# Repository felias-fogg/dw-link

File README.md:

# dw-link 

This Arduino sketch turns your Arduino UNO into a hardware debugger for the classic ATtinys and the ATmegaX8s, such as the ATmega328. It gives you a chance to find out how it feels to use a source-level debugger on an Arduino Uno or an ATtiny board. Do you want to give it a try? Use the *quick-start guide* in the [dw-link manual](https://felias-fogg.github.io/dw-link/) to see if it works for you. 

From version 7 on, the protocol has been changed from [GDB RSP](https://sourceware.org/gdb/current/onlinedocs/gdb.html/Remote-Protocol.html) to a variant of the JTAGICE mkII protocol ([AVR067](https://www.microchip.com/en-us/application-notes/an2587-1)), which implies that you necessarily have to use [PyAvrOCD](https://pyavrocd.io) (version >= 2.0.0) as a GDB server. If you want to connect GDB to dw-link using only the serial line, you need to fall back to version 6.

This repository, which is organized as an Arduino library, contains the following directories:

* [**src**](src/) contains an empty header file so that it fits the format of a library,
* [**examples**](examples/) contains 
  * the [dw-link](examples/dw-link/) sketch, the debugger firmware, and 
  * the [testprobe](examples/testprobe/) sketch, which can be used to run tests on a freshly assembled dw-link probe shield,
* [**docs**](docs/) contains the documentation files for the [manual](https://felias-fogg.github.io/dw-link/),
* [**extras**](extras/) contains the folder [pcb](extras/pcb/) with design data (KiCad) for the optional dw-link probe.

<sup><sub>The cover picture was designed based on vector graphics by [captainvector at 123RF](https://de.123rf.com/profile_captainvector).</sub></sup>

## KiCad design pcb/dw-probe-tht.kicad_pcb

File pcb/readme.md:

# The *dw-link probe*: Hardware for dw-link

<br />This work is licensed under a <a rel="license" href="http://creativecommons.org/licenses/by/4.0/">Creative Commons Attribution 4.0 International License</a>.

When you want to debug your projects using dw-link more than once, it is a good idea to have a hardware solution. For instance, an Arduino shield. As described in the manual, you can just assemble a solution on a prototype board, which works for 5 V projects with less than 20 mA of supply current. 

The current design of the *dw-link probe* is more ambitious, but far from an industrial-strength hardware debugging tool as, e.g., Atmel ICE. The limitations for the target boards are:

* 3.3 to 5 V supply voltage (but not lower),
* reasonable loads on the SPI lines, e.g., an LED and a 1 kΩ series resistor (but no stronger resistor),
* no capacitive load on the RESET line of the target,
* no loads higher than a 10 kΩ resistance on the RESET line,
* minimum target MCU clock frequency of 4 kHz.

If these constraints are met, the dw-link probe should work.  Otherwise, one might encounter strange behavior and/or error messages. 

The current version (V3.1) of the dw-link probe (an Arduino UNO shield) uses mainly THT components, which should make it easy to assemble it using [these instructions](assembly.md). The three SMD components can also be hand-soldered to the PCB since the solder pads are extra large. 

**Note:** It is advisable to solder an additional 100 µF or more capacitor between 5V and GND. Otherwise, the hardware debugger might brown out when power-cycling the target, and you will need to disconnect and reconnect.

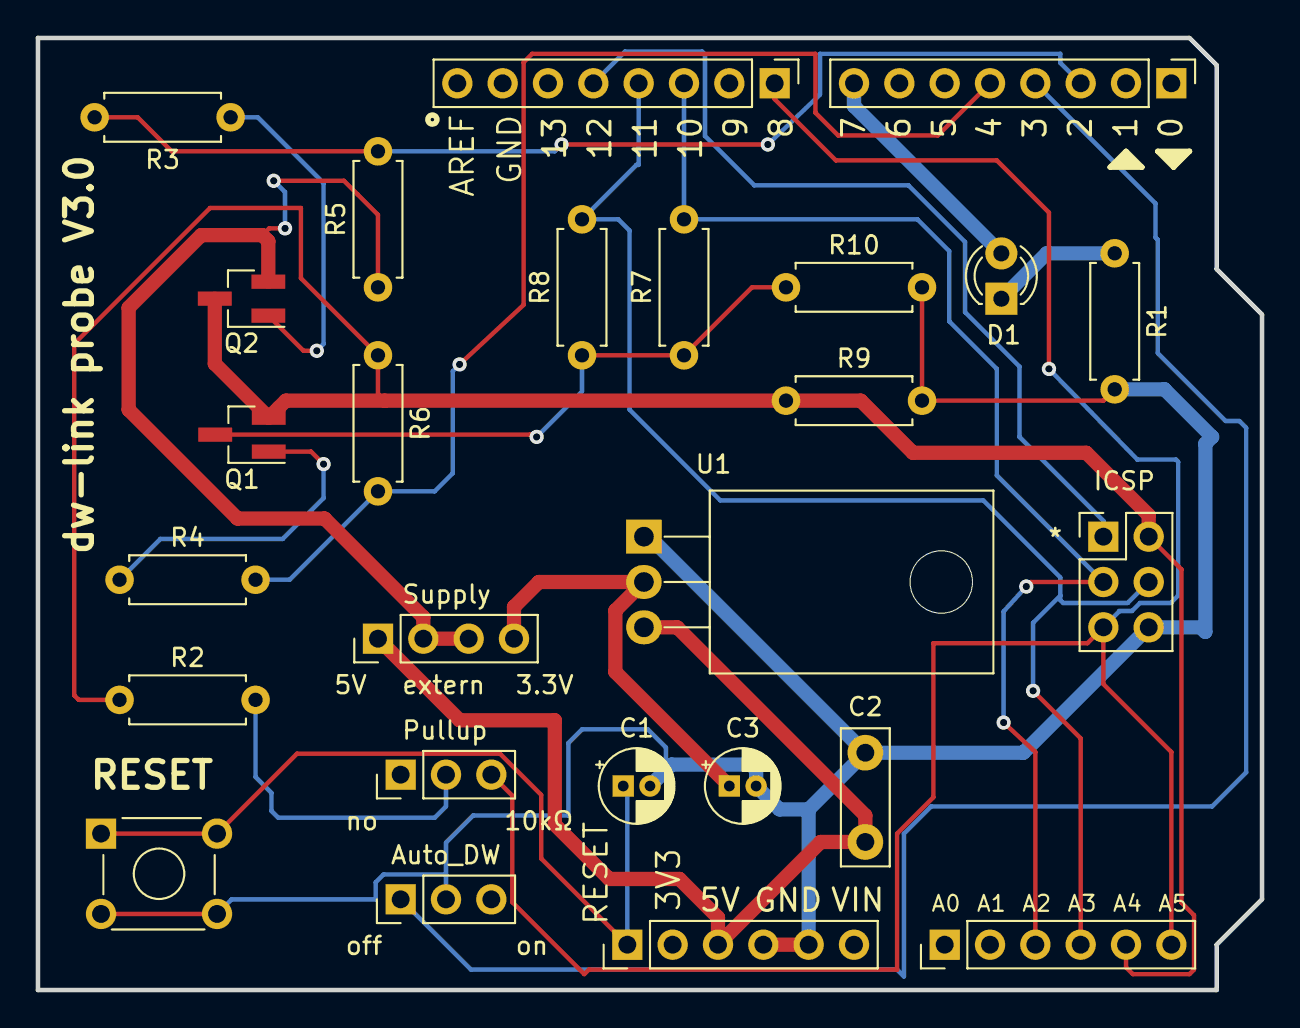
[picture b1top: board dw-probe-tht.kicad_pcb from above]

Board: 2 copper layers, 68.6 x 53.3 mm, 26 parts (0 on the bottom side), 19 nets.

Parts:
AD1: PINHD-1X6; PinHeader_1x06_P2.54mm_Vertical
Auto_DW1: Conn_01x03; PinHeader_1x03_P2.54mm_Vertical
C1, C3: 10µF; CP_Radial_D4.0mm_P1.50mm
C2: 100nF; C_Disc_D7.5mm_W2.5mm_P5.00mm
D1: LED; LED_D3.0mm
IOH1: PINHD-1X8; PinHeader_1x08_P2.54mm_Vertical
IOL1: PINHD-1X8; PinHeader_1x08_P2.54mm_Vertical
JP1: ARDUINO_CONN-ICSP; PinHeader_2x03_P2.54mm_Vertical
POWER1: PINHD-1X6; PinHeader_1x06_P2.54mm_Vertical
Pullup1: Conn_01x03; PinHeader_1x03_P2.54mm_Vertical
Q1, Q2: IRLML6402; SOT-23_Handsoldering
R1: 1kΩ; R_Axial_DIN0207_L6.3mm_D2.5mm_P7.62mm_Horizontal
R2, R5, R6: 10kΩ; R_Axial_DIN0207_L6.3mm_D2.5mm_P7.62mm_Horizontal
R3, R4: 220Ω; R_Axial_DIN0207_L6.3mm_D2.5mm_P7.62mm_Horizontal
R7, R8: 680Ω; R_Axial_DIN0207_L6.3mm_D2.5mm_P7.62mm_Horizontal
R9, R10: 10MΩ; R_Axial_DIN0207_L6.3mm_D2.5mm_P7.62mm_Horizontal
SW1: SW_Push; SW_TH_Tactile_Omron_B3F-10xx
Supply1: Conn_01x04; PinHeader_1x04_P2.54mm_Vertical
U1: LM1117T-3.3; TO-220-3_Horizontal_TabDown

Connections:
GND: Auto_DW1.2, C1.2, C2.2, C3.2, IOH1.7, JP1.6, POWER1.4, POWER1.5, R1.2, R9.2, R10.2, SW1.2, U1.1 (GND)
unnamed: AD1.3, IOH1.3, JP1.3, R7.2
unnamed: AD1.4, IOH1.4, JP1.4, R8.2
unnamed: Auto_DW1.1, IOL1.4
unnamed: C1.1, POWER1.1, SW1.1
unnamed: D1.2 (A), IOL1.8
unnamed: D1.1 (K), R1.1
unnamed: IOH1.5, JP1.1
unnamed: IOL1.3, R3.2, R5.2
unnamed: IOL1.5, R4.2, R6.2
unnamed: Pullup1.2, R2.2
unnamed: AD1.6, IOH1.1, JP1.5, Pullup1.3
unnamed: Q1.3 (D), R7.1, R8.1, R10.1
unnamed: Q1.1 (G), R4.1
unnamed: Q2.1 (G), R3.1
unnamed: Q2.2 (S), R5.1, Supply1.2, Supply1.3
unnamed: C2.1, POWER1.3, Supply1.1, U1.3 (VI)
unnamed: C3.1, Supply1.4, U1.2 (VO)
VCC: AD1.5, JP1.2, Q1.2 (S), Q2.3 (D), R2.1, R6.1, R9.1

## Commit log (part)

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2021-11-24 V 1.0.2 - without build files
2021-11-30 V1.0.3
2021-12-02 V1.0.4
2021-12-04 V1.0.5
2021-12-07 V1.0.6
2021-12-10 V1.0.7
2021-12-11 V1.0.8
2021-12-20 V1.0.9
2021-12-27 V1.1.0
2021-12-29 V1.1.1
2021-12-30 V1.1.2
2021-12-30 V1.1.3
2021-12-31 V1.1.4 - public release
2021-12-31 changelog updated
2021-12-31 readme updated
2021-12-31 added workflow
2021-12-31 corrected workflow
2021-12-31 V1.1.5
2022-01-03 V1.1.6
2022-01-03 V1.1.6 - missing pic
2022-01-03 V1.1.6 - workflow change
2022-01-03 V1.1.6 - unit tests removed
2022-01-03 V1.1.6 - workflow changed
2022-01-04 V1.1.7
2022-01-04 V1.1.8
2022-01-05 V1.1.9
2022-01-05 V1.1.9 - updated docu
2022-01-05 V1.1.10
2022-01-06 manual update
2022-01-08 update pcb and doc
2022-01-08 blockusb branch
2022-01-09 V1.1.11
2022-01-09 pic update
2022-01-09 updated workflow
2022-01-11 V1.1.12
2022-01-11 V1.1.12 - dwlink nano fix
2022-01-15 V1.2.0
2022-01-15 V1.2.0.a
2022-01-15 V1.2.1
2022-01-15 V1.2.2
2022-01-17 V1.2.3
2022-01-17 V1.2.4
2022-01-17 manual - wiring fix
2022-01-19 V1.2.5
2022-01-19 V1.2.5 - workflow
2022-01-19 V1.3.0
2022-01-20 V1.3.1
2022-01-20 V1.3.2
2022-01-20 V1.3.3
2022-01-22 V1.3.4
2022-01-23 V1.3.5
2022-01-26 V1.3.6
2022-02-02 V1.3.7
2022-02-02 optimized PDF file
2022-02-02 V1.3.7 (updated)
2022-02-02 V1.3.7 (manual updated)
2022-02-04 V1.3.8
2022-02-17 V1.3.9
2022-03-12 platformio debugging calls 'mo dwconnect'
2022-03-12 V1.3.10
2022-03-13 Changed gitignore
2022-11-24 Disable pull up on TMOSI upon disableSpiPins()
2023-01-07 Added symbolic link from src to dw-link to make platformio build possible
2023-08-11 V2.0.0
2023-08-11 fixed some inconsistencies
2023-08-15 V2.1.0
2023-08-15 V2.1.2
2023-08-15 V2.1.2 (incl. documentation)
2023-08-16 V2.1.3
2023-08-16 V2.1.4
2023-08-17 V2.1.5
2023-08-18 V 2.1.6
2023-08-20 V2.1.7
2023-08-21 V2.1.8
2023-08-22 dw-server and documentation
2023-08-22 fixed typos in quickstart
2023-08-22 readme fixes
2023-08-22 quzickstart fixes
2023-08-23 added checks to quickstart
2023-08-23 V2.1.9
2023-08-23 readme fix
2023-08-24 docu update
2023-08-24 workflow update
2023-08-26 changelog ficed
2023-08-26 Revert "workflow update"
    This reverts commit 78d8907c8fad9df0ea710d77213ca2aa1fff75bf.
2023-08-26 re-apply workflow changes
2023-08-27 docu extended
2023-08-27 pcb fix
2023-08-27 .gitignore removed from repo
2023-08-27 V2.2.0
2023-08-27 V2.2.1
2023-08-28 V2.3.0
2023-08-28 V3.0.0
2023-08-28 changelog
2023-08-28 manual fix
2023-08-28 .gitignore
2023-08-29 V3.0.1
2023-08-29 quickstart pdf
2023-08-29 quickstart update
2023-08-29 Manual and Quickstart fixes
2023-08-29 Quickstart fixes
2023-08-29 quickstart
2023-09-05 V3.1.0
2023-09-06 V3.1.1
2023-09-06 readme
2023-09-06 docs
2023-09-09 PCB & docu
2023-09-10 documentation update
2023-09-11 assembly update
2023-09-11 V3.3.0
2023-09-11 changelog fix
2023-09-11 CS2 fix
2023-09-12 V3.4.0
2023-09-13 low frequency
2023-09-13 V3.5.0
2023-09-13 V3.5.1
2023-09-15 V3.5.2
2023-09-18 testprobe
2023-09-20 new dw-link probe V3.1
2023-09-20 new example, restored pics
2023-09-21 description of debugging UNO with serial connection
2023-09-21 adapted to new gede version
2023-09-22 manual toubleshooting: ISP programmer failure
2023-09-23 V3.5.3
2023-09-23 going back to my version of gede
2023-09-25 readme update
2023-10-05 manual
2023-12-18 documentation adapted, in particular new schemativ for probe
2024-02-25 V3.5.4
2024-12-16 V3.5.5
2024-12-16 quickstart.pdf update
2024-12-17 V3.5.6
2024-12-23 V4.0.0 - with Arduino IDE 2.0 support
2024-12-28 V4.0.0
2024-12-29 all tool files ready to roll
2024-12-29 tools files moved to felias-fogg.github.io
2024-12-30 added quickstart link
2024-12-30 edited quickstarts
2024-12-31 core mods adapted, MiniCore works
2024-12-31 readme updates + core-mods fixes
2025-01-01 V4.0.1
2025-01-02 V4.0.2
2025-01-02 update manual
2025-01-06 V4.0.3
2025-01-06 updated docs + dw-server for Linux
2025-01-07 assembly notes adapted and testprobe.ino extended
2025-01-07 quickstart hardlink
2025-01-07 update doc because of windows hickup
2025-01-08 doc update and Windows tool issue mitigation
2025-01-08 doc update
2025-01-16 V4.0.4
2025-01-18 V4.1.0
2025-01-19 V4.2.0
2025-01-19 update changelog
2025-02-01 V4.3.0
2025-02-01 V4.3.1
2025-02-10 V4.4.0
2025-02-14 manual V4.4.0
2025-02-26 V4.5.0
2025-03-27 V5.0.0-pre1
2025-03-28 v5.0.0-pre2
2025-04-16 v5.0.0
2025-04-17 v5.1.0
2025-07-22 v5.2.0
2025-07-29 ISPMON removed
2025-07-30 v5.2.1
2025-07-31 v5.2.2
2025-08-01 v5.2.3
2025-08-18 v5.2.4
2025-09-26 Deployed 45a31e7 with MkDocs version: 1.6.1
2025-09-26 mkdocs
2025-09-26 Deployed 1673c36 with MkDocs version: 1.6.1
2025-09-26 Deployed 426f6d8 with MkDocs version: 1.6.1
2025-10-04 Deployed e834845 with MkDocs version: 1.6.1
2025-10-04 Deployed f349ee1 with MkDocs version: 1.6.1
2025-11-23 Deployed 1fbc1d6 with MkDocs version: 1.6.1
2025-12-07 v5.3.0
2025-12-07 Deployed f28f431 with MkDocs version: 1.6.1
2025-12-13 v5.4.0
2025-12-16 Deployed 3473d8e with MkDocs version: 1.6.1
2025-12-16 Deployed e3ad75b with MkDocs version: 1.6.1
2025-12-17 v6.0.0
2025-12-17 v6.0.1
2025-12-17 workflof: exclude nano
2025-12-17 workflow: exclude nano
2025-12-17 Deployed 749f7cd with MkDocs version: 1.6.1
2025-12-27 dw-uploader
2025-12-27 monitor commands adapted to PyAvrOCD conventions
2025-12-27 new build workflow
2025-12-27 workflow
2025-12-28 workflow for dw-uploader ready
2025-12-28 workflow fix
2025-12-28 v6.0.2
2025-12-28 workflow and pyintstaller fix
2025-12-28 docs fw-upload
2025-12-28 Deployed 1be1a03 with MkDocs version: 1.6.1
2025-12-30 v6.0.3
2025-12-30 v6.0.3 docs
2025-12-30 Deployed 85ff878 with MkDocs version: 1.6.1
2026-01-26 v6.1.0
2026-01-31 Deployed 478c51d with MkDocs version: 1.6.1
2026-01-31 no modw
2026-02-15 Deployed 124e81a with MkDocs version: 1.6.1
2026-02-15 typos, .gitignore, and dw-uploader
2026-04-07 replace ATTinyCore by TinyCore in docs
2026-04-07 Deployed 86a4c79 with MkDocs version: 1.6.1
2026-04-07 docs update
2026-04-07 Deployed ea6e4c1 with MkDocs version: 1.6.1
2026-04-07 Deployed f506cd0 with MkDocs version: 1.6.1
2026-04-11 Deployed ea6aefb with MkDocs version: 1.6.1

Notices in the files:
README.md:
License: GPL v3
License: CCBY4.0
